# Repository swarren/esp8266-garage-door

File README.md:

# ESP8266 Internet Garage Door Opener

This repo contains all the design files relate to the ESP8266-based garage
door opener project I recently created. My basic requirements were:

- Be functonal and deployed as quickly as possible, rather than being as clean
and well-engineered as possible.

- Not interfere with the electronics of my existing manual-switch-triggered
opener.

Quick list of features/parts:

- ESP8266 WiFi SoC for the Internet connection. NodeMCU board.

- Arduino-based software stack.

- HTTP/HTML-based user interface.

- WiFi credentials entered at "run-time" using a web browser and saved to
flash, rather than being hard-coded into the application code.

- PCB created in Kicad to mount the ESP8266 and connectors.

- Standalone commercial relay board to trigger the door opener.

- HC-SR04 sensors used to detect whether the door is open or closed.

- HC-SR04 wall mounts designed using OpenSCAD and 3D-printed.

Look on my blog at http://rabbithole.wwwdotorg.org for more details.

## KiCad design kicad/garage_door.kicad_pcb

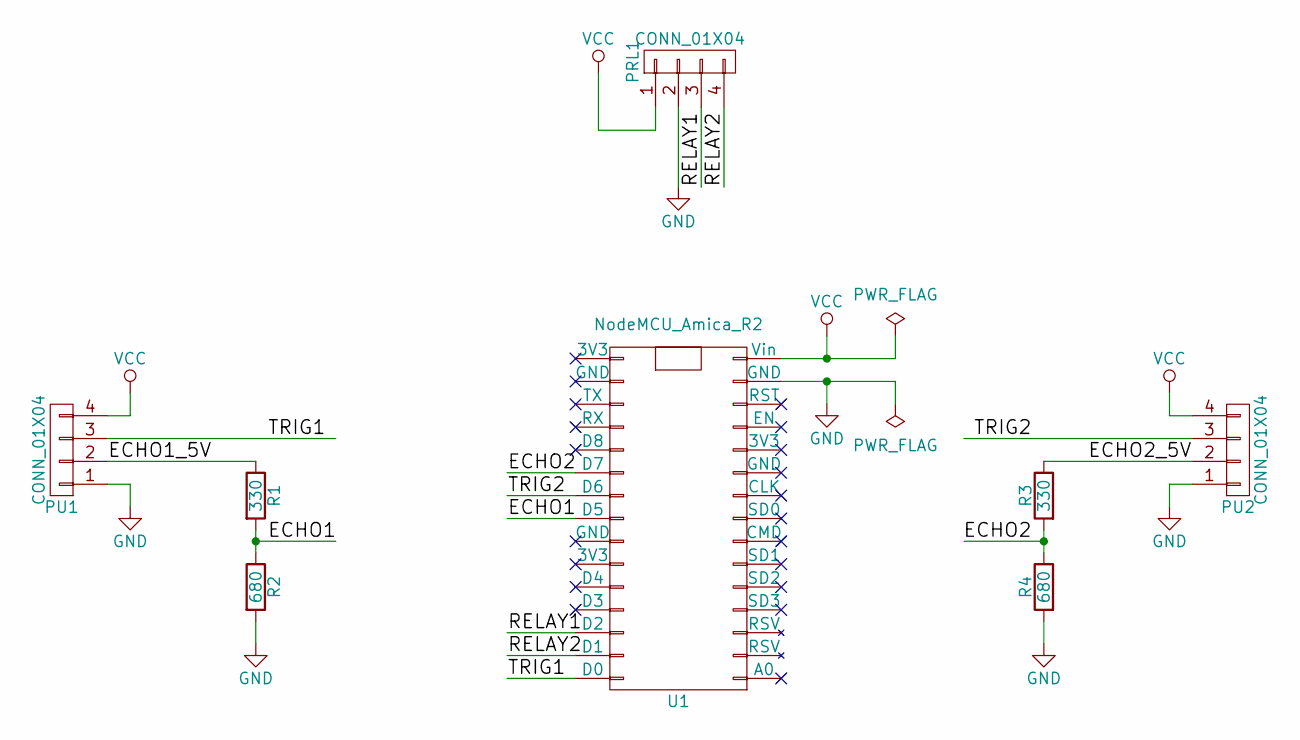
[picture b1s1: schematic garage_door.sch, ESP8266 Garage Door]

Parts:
PRL1: CONN_01X04; Pin_Header_Angled_1x04_Pitch2.54mm
PU1, PU2: CONN_01X04; Pin_Header_Angled_1x04_Pitch2.54mm
R1, R3: 330; R_Axial_DIN0207_L6.3mm_D2.5mm_P10.16mm_Horizontal
R2, R4: 680; R_Axial_DIN0207_L6.3mm_D2.5mm_P10.16mm_Horizontal
U1: NodeMCU_Amica_R2

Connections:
/ECHO1: R1.2, R2.1, U1.23 (D5)
/ECHO1_5V: PU1.2, R1.1
/ECHO2: R3.2, R4.1, U1.21 (D7)
/ECHO2_5V: PU2.2, R3.1
/RELAY1: PRL1.3, U1.28 (D2)
/RELAY2: PRL1.4, U1.29 (D1)
/TRIG1: PU1.3, U1.30 (D0)
/TRIG2: PU2.3, U1.22 (D6)
GND: PRL1.2, PU1.1, PU2.1, R2.2, R4.2, U1.14 (GND)
VCC: PRL1.1, PU1.4, PU2.4, U1.15 (Vin)

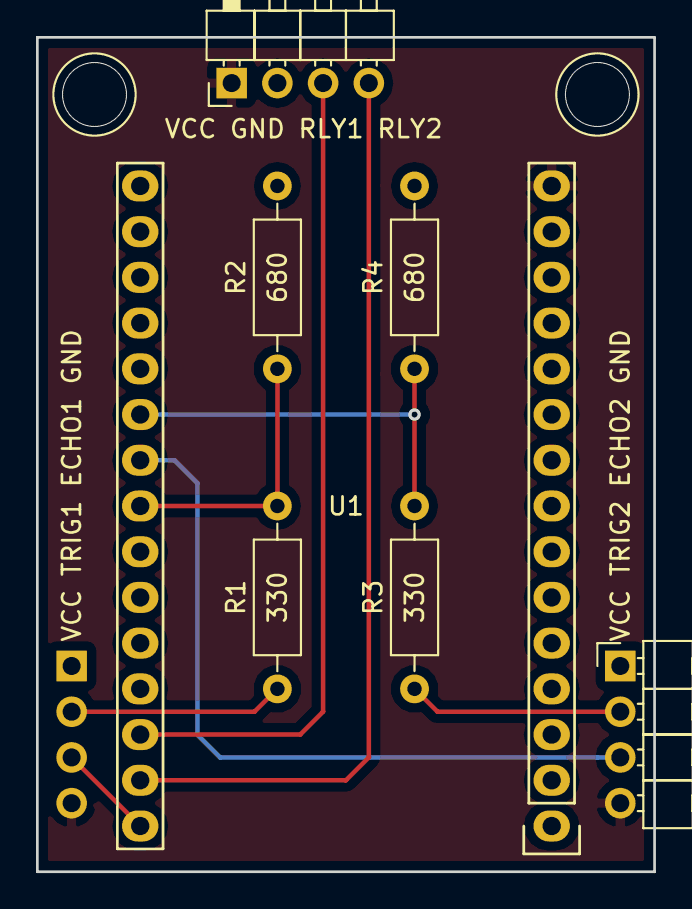
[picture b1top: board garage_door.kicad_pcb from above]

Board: 2 copper layers, 34.3 x 46.4 mm, 8 parts (1 on the bottom side), 10 nets.

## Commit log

2017-04-19 Initial version
2017-04-25 Rev 2 PCB updates
    - Rev 2 PCB tested on main garage door; remove untested comment.
    - Deploy rev 1 PCB to third garage door; update its config stanza.
    Ultrasound sensor still needs physical wiring, but the SW is prepared.
    - Move Arduino code into a sub-dir with matching name so the IDE doesn't
    complain about the directory name:-/
    - Remove vi temp file, add .gitignore file for them.
2017-05-11 Fix cut/paste mistake in license headers
2017-06-17 Control relays via a state machine
    This avoids synchronously blocking in the POST handler, which should
    improve responsiveness of the web server an IP stack in general
    immediately after a request to active a door.
2018-01-03 Display sensor history in HTML
    This makes it easier to see what state the door is in, since each
    individual ping result can be seen.
2018-01-05 Send email when door opens/closes
    This is enough to work, but the code is pretty icky.
    TODO:
    - Get SMTP parameters via /setup URL rather than hard-coding them.
    - Share code between the many SMTP state; likely by creating an array
    of RX/TX lines and simply iterating over it.
    - Read SMTP spec to determine whether it's OK to hard-code the response
2018-01-06 SMTP reliability and consolidation
    - AsyncClient randomly fires onDisconnect() callbacks if it's re-used for
    multiple connections. Create/Destroy it for each transaction to avoid
    this.
    - This means that the AsyncClient callbacks must be set each time the
    AsyncClient is created. Using closures for this seems to leak memory.
    Use static _on_xxx() callback implementations to avoid this.
2018-01-07 Fix third garage ultrasound echo time
    The ultrasound device placement is different on the third door, being
    aimed at the side of the door through a narrow gap. This yields very short
    positive ping times. Unfortunately, other material such as a rubber draft
    flap sometimes bend into the path of the ultrasound and creates false
    positive closed indications. To prevent this, only accept very close ping
    times for this door.
2019-10-03 Fix OpenSCAD file copyright comment format
